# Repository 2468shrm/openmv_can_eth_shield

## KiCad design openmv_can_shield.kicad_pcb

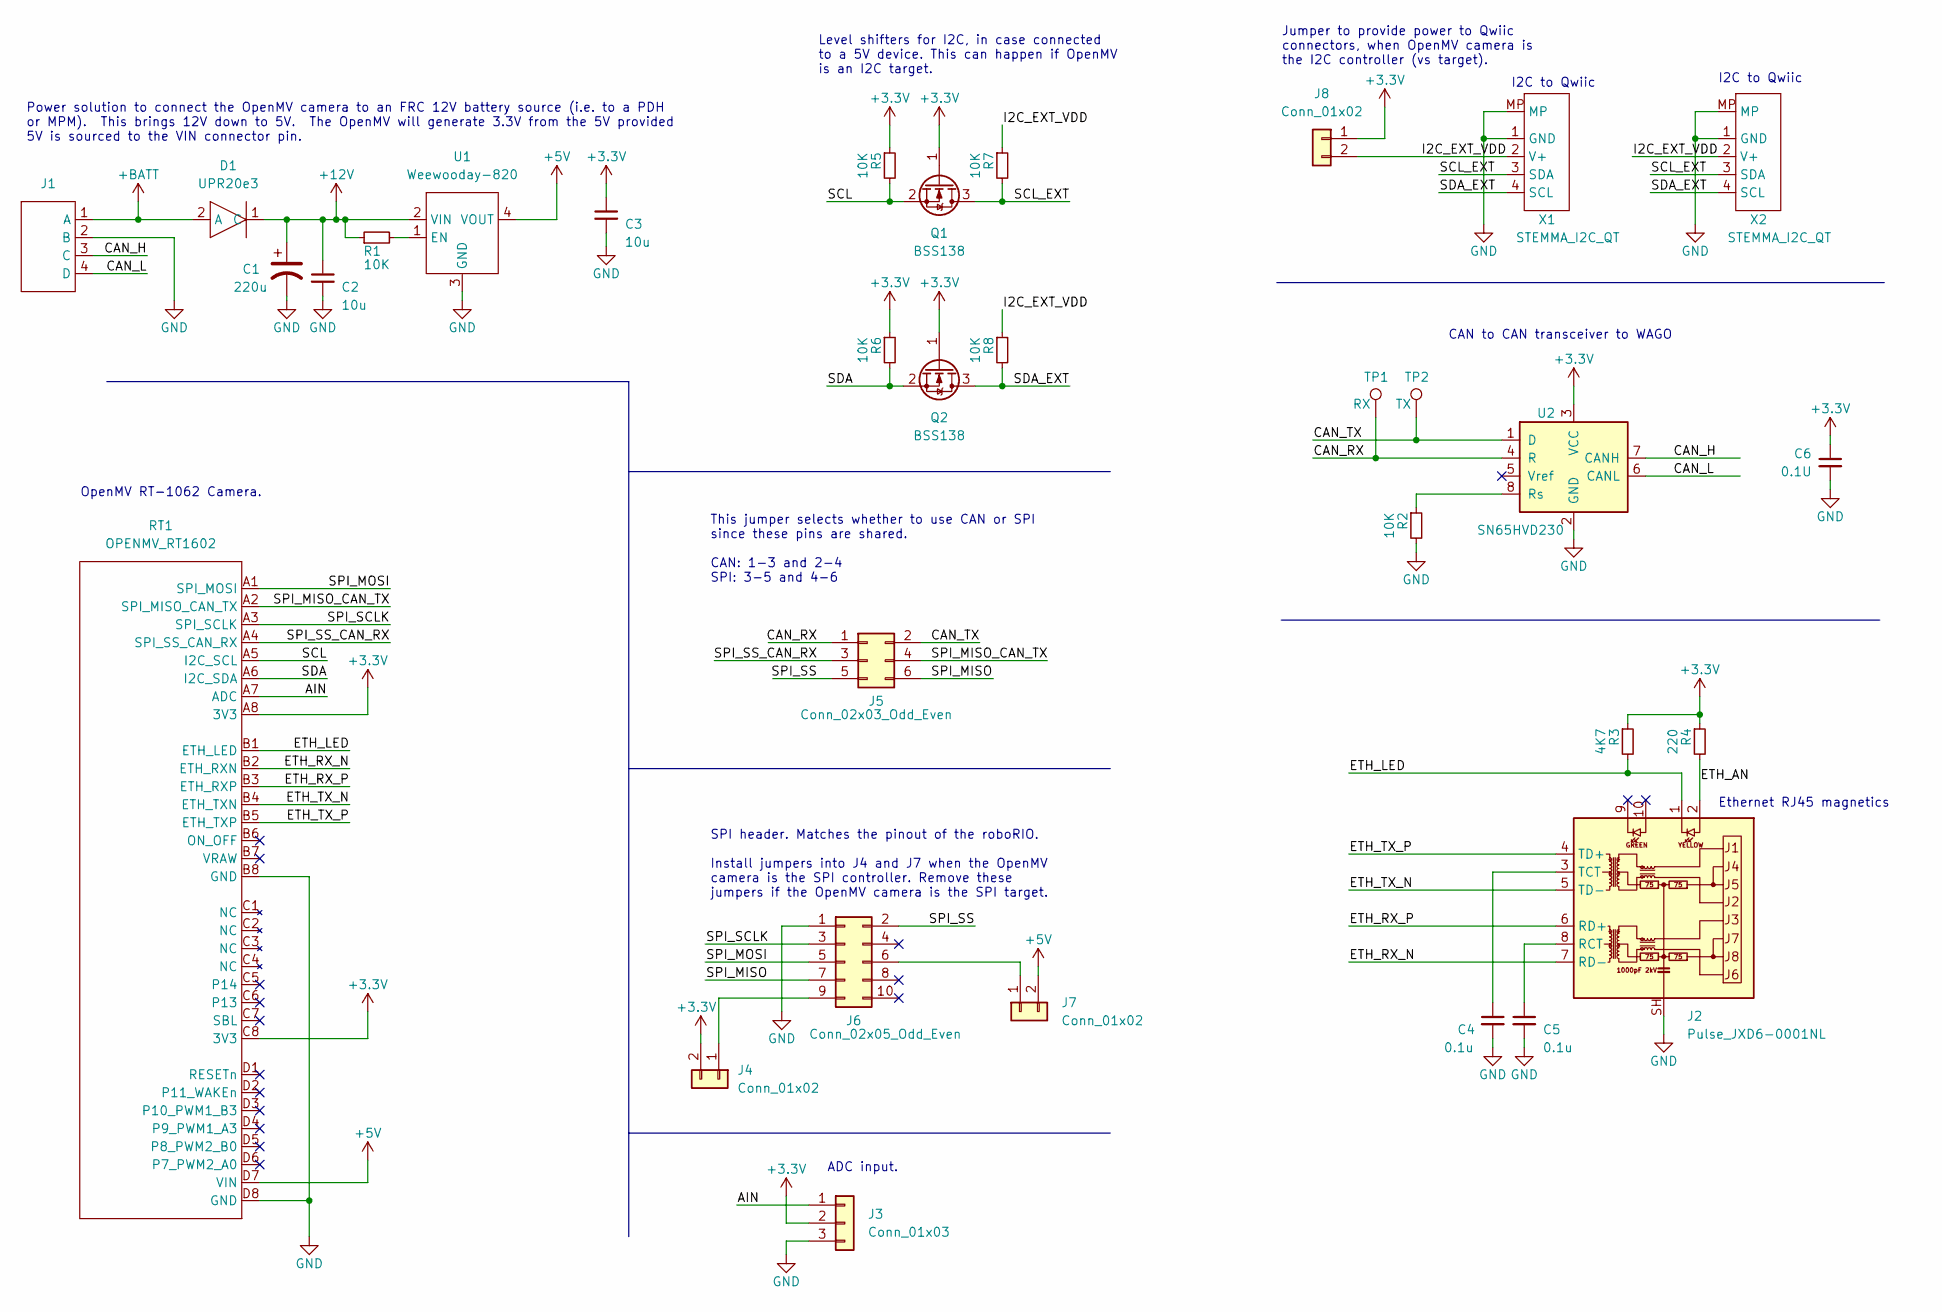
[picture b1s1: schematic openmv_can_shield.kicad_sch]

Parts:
C1: 220u; CP_Elec_6.3x7.7; LCSC C340767
C2, C3: 10u; C_1206_3216Metric; LCSC C14860
C4, C5: 0.1u; C_1206_3216Metric; LCSC C14860
C6: 0.1U; C_1206_3216Metric
D1: UPR20e3; DO-216
J1: WAGO_250-204; WAGO 250-204
J2: Pulse_JXD6-0001NL; RJ45_Pulse_JXD6-0001NL_Horizontal
J3: Conn_01x03; PinHeader_1x03_P2.54mm_Vertical
J4, J7, J8: Conn_01x02; PinHeader_1x02_P2.54mm_Vertical
J5: Conn_02x03_Odd_Even; PinHeader_2x03_P2.54mm_Vertical
J6: Conn_02x05_Odd_Even; PinHeader_2x05_P2.54mm_Vertical
Q1, Q2: BSS138; SOT-23
R1, R2, R5, R6, R7, R8: 10K; R_1206_3216Metric
R3: 4K7; R_1206_3216Metric
R4: 220; R_1206_3216Metric
RT1: OPENMV_RT1602; RT1062
TP1: RX; TestPoint_Pad_D1.5mm
TP2: TX; TestPoint_Pad_D1.5mm
U1: Weewooday-820
U2: SN65HVD230; SOIC-8_3.9x4.9mm_P1.27mm
X1, X2: STEMMA_I2C_QT; JST_SH_BM04B-SRSS-TB_1x04-1MP_P1.00mm_Vertical; LCSC C545725

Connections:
+3.3V: C3.1, C6.1, J3.2, J4.2, J8.1, Q1.1 (G), Q2.1 (G), R3.1, R4.1, R5.1, R6.1, RT1.A8 (3V3), RT1.C8 (3V3), U2.3 (VCC)
+5V: J7.2, RT1.D7 (VIN), U1.4 (VOUT)
+12V: C1.1, C2.1, D1.1 (C), R1.1, U1.2 (VIN)
+BATT: D1.2 (A), J1.1 (A)
/AIN: J3.1, RT1.A7 (ADC)
/CAN_H: J1.3 (C), U2.7 (CANH)
/CAN_L: J1.4 (D), U2.6 (CANL)
/CAN_RX: J5.1, TP1.1, U2.4 (R)
/CAN_TX: J5.2, TP2.1, U2.1 (D)
/ETH_AN: J2.2, R4.2
/ETH_LED: J2.1, R3.2, RT1.B1 (ETH_LED)
/ETH_RX_N: J2.7 (RD-), RT1.B2 (ETH_RXN)
/ETH_RX_P: J2.6 (RD+), RT1.B3 (ETH_RXP)
/ETH_TX_N: J2.5 (TD-), RT1.B4 (ETH_TXN)
/ETH_TX_P: J2.4 (TD+), RT1.B5 (ETH_TXP)
/I2C_EXT_VDD: J8.2, R7.1, R8.1, X1.2 (V+), X2.2 (V+)
/SCL: Q1.2 (S), R5.2, RT1.A5 (I2C_SCL)
/SCL_EXT: Q1.3 (D), R7.2, X1.3 (SDA), X2.3 (SDA)
/SDA: Q2.2 (S), R6.2, RT1.A6 (I2C_SDA)
/SDA_EXT: Q2.3 (D), R8.2, X1.4 (SCL), X2.4 (SCL)
/SPI_MISO: J5.6, J6.7
/SPI_MISO_CAN_TX: J5.4, RT1.A2 (SPI_MISO_CAN_TX)
/SPI_MOSI: J6.5, RT1.A1 (SPI_MOSI)
/SPI_SCLK: J6.3, RT1.A3 (SPI_SCLK)
/SPI_SS: J5.5, J6.2
/SPI_SS_CAN_RX: J5.3, RT1.A4 (SPI_SS_CAN_RX)
GND: C1.2, C2.2, C3.2, C4.2, C5.2, C6.2, J1.2 (B), J2.SH, J3.3, J6.1, R2.2, RT1.B8 (GND), RT1.D8 (GND), U1.3 (GND), U2.2 (GND), X1.1 (GND), X1.MP, X2.1 (GND), X2.MP
unnamed: C4.1, J2.3 (TCT)
unnamed: C5.1, J2.8 (RCT)
unnamed: J4.1, J6.9
unnamed: J6.6, J7.1
unnamed: R1.2, U1.1 (EN)
unnamed: R2.1, U2.8 (Rs)

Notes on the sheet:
ADC input.
Ethernet RJ45 magnetics
This jumper selects whether to use CAN or SPI since these pins are shared. CAN: 1-3 and 2-4 SPI: 3-5 and 4-6
Level shifters for I2C, in case connected to a 5V device. This can happen if OpenMV is an I2C target.
CAN to CAN transceiver to WAGO
OpenMV RT-1062 Camera.
SPI header. Matches the pinout of the roboRIO. Install jumpers into J4 and J7 when the OpenMV camera is the SPI controller. Remove these jumpers if the OpenMV camera is the SPI target.
Power solution to connect the OpenMV camera to an FRC 12V battery source (i.e. to a PDH or MPM). This brings 12V down to 5V. The OpenMV will generate 3.3V from the 5V provided 5V is sourced to the VIN connector pin.
Jumper to provide power to Qwiic connectors, when OpenMV camera is the I2C controller (vs target).
I2C to Qwiic

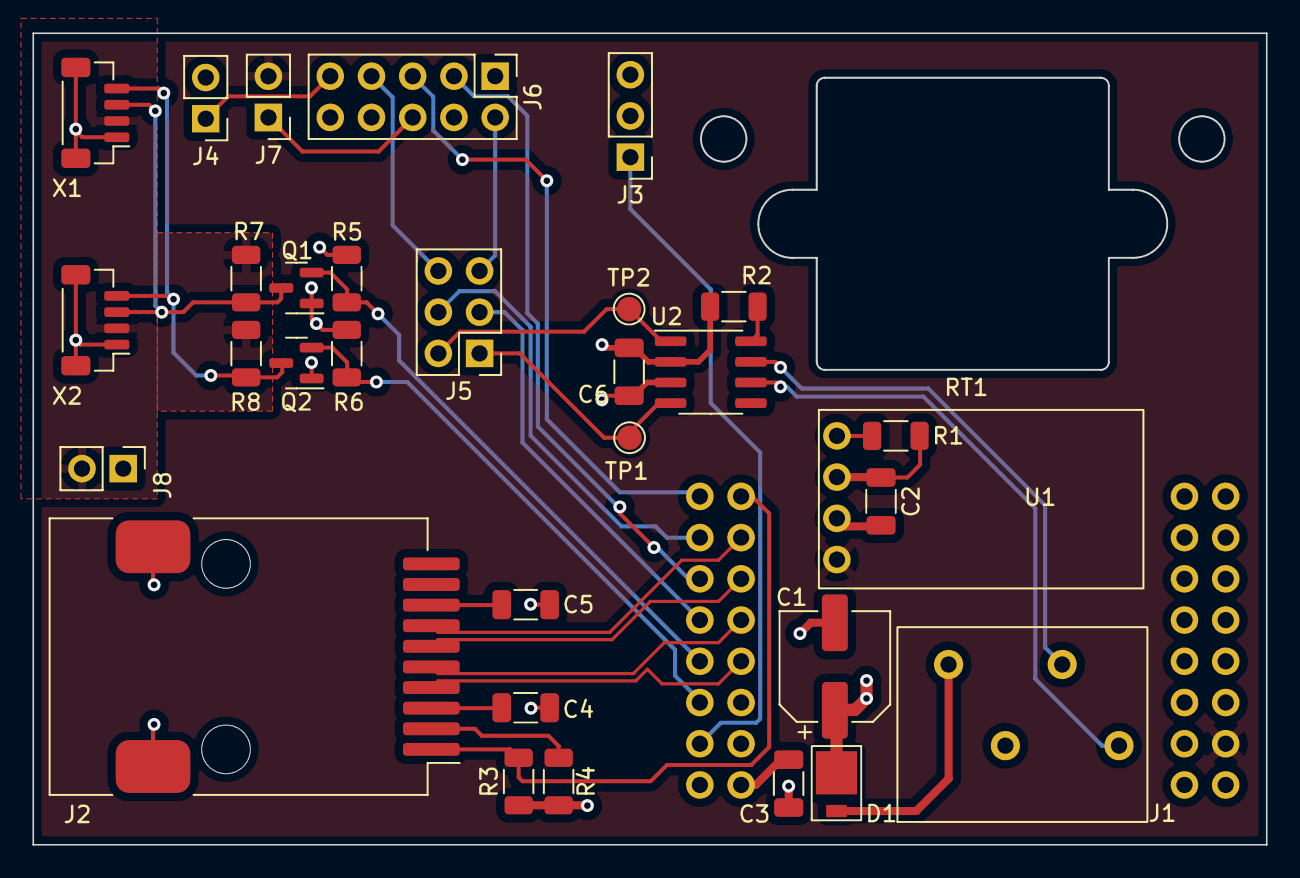
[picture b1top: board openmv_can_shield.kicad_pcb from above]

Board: 4 copper layers, 76.0 x 50.0 mm, 32 parts (0 on the bottom side), 33 nets.

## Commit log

2024-02-24 PCB files
2024-02-28 Updated schematics and layout to have complete, DRC clean layout, Gerbers not updated
